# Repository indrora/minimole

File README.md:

# miniMOLE: the miniature Modular Output for Legacy Electronics.

the MiniMOLE is a tiny power supply for powering hard drives, floppy drives, etc. on the go. 

The power supplies that a lot of powerable HDD docks come with are just not good enough to handle some drives. Other times, you need something that doesn't fit in one of those docks. 

The miniMOLE is here for that: Either use a cablemod RT/Seasonic style modular peripheral cable or the included push-fit connectors for custom stuff. 

## fab notes:

* 2oz copper
* OSP or ENIG finish
* Everything has a JLCPCB part number.

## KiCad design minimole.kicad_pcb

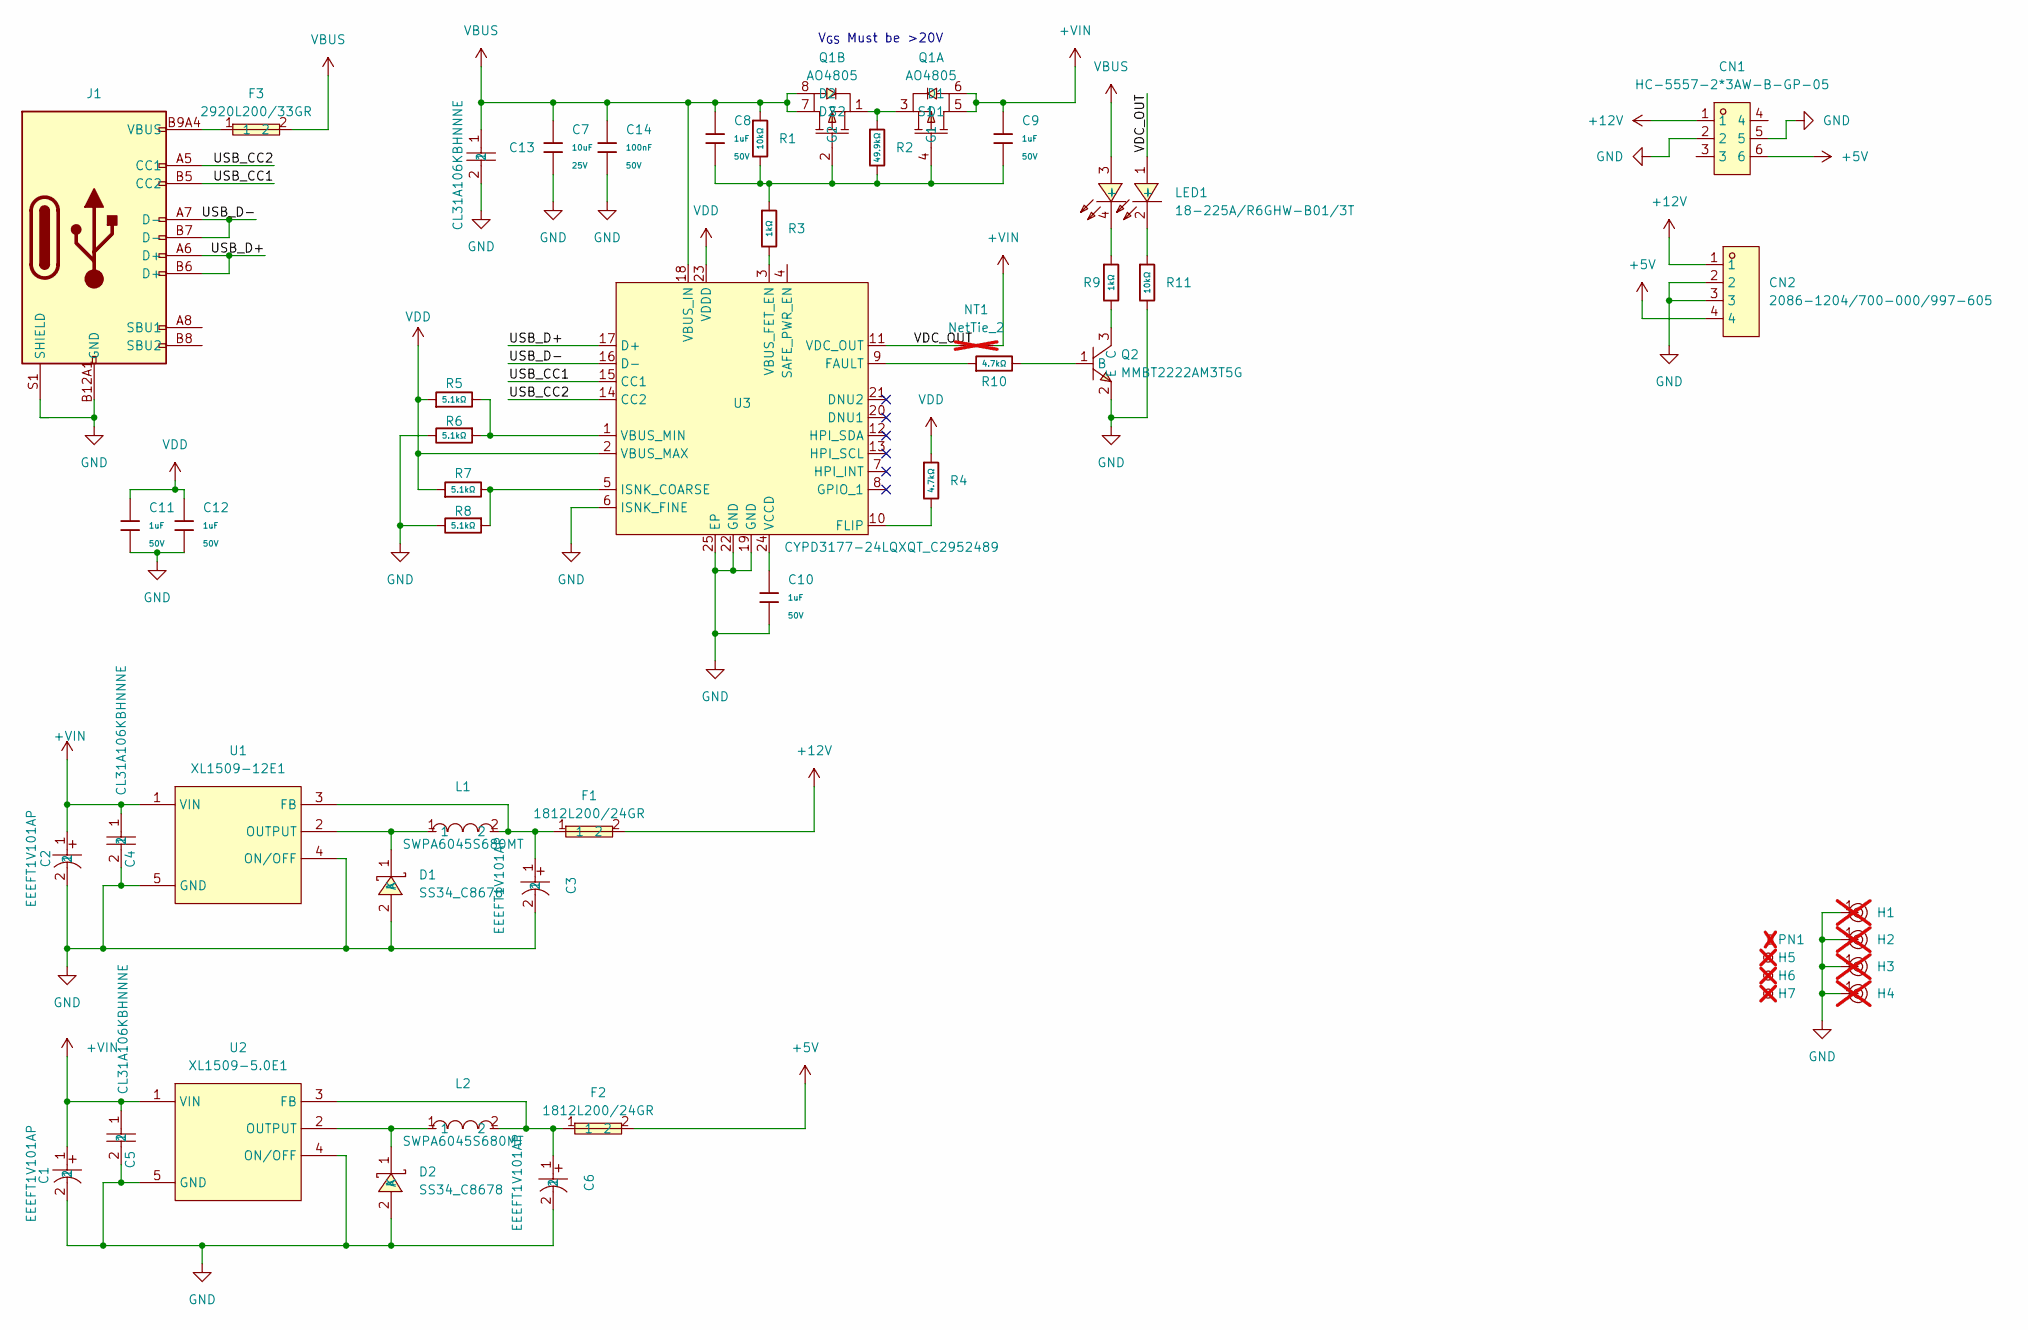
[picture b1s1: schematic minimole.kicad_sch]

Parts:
C1, C2, C3, C6: EEEFT1V101AP; CAP-SMD_BD6.3-L6.6-W6.6-FD; MPN EEEFT1V101AP; LCSC Part C128464
C4, C5, C13: CL31A106KBHNNNE; C1206; MPN CL31A106KBHNNNE; LCSC Part C13585
C7: 10uF; C_0603; Voltage Rated 25V; Tolerance ±20%; Part CL10A106MA8NRNC; LCSC C96446
C8, C9, C10, C11, C12: 1uF; C_0603; Voltage Rated 50V; Tolerance ±10%; Part CL10A105KB8NNNC; LCSC C15849
C14: 100nF; C_0603; Voltage Rated 50V; Tolerance ±10%; Part CC0603KRX7R9BB104; LCSC C14663
CN1: HC-5557-2*3AW-B-GP-05; CONN-TH_6P-P4.20_HCTL_HC-5557-2X3AW-B-GP-05; MPN HC-5557-2*3AW-B-GP-05; LCSC Part C22398227
CN2: 2086-1204/700-000/997-605; CONN-SMD_4P-P3.50_2086-1204; MPN 2086-1204/700-000/997-605; LCSC Part C3309718
D1, D2: SS34_C8678; SMA_L4.3-W2.6-LS5.2-RD; MPN SS34; LCSC Part C8678
F1, F2: 1812L200/24GR; F1812; MPN 1812L200/24GR; LCSC Part C18198341
F3: 2920L200/33GR; F2920; MPN 2920L200/33GR; LCSC Part C19078743
H1, H2, H3, H4: Hole, 3mm; not fitted
H5, H6, H7: Hole_Tooling_JLCPCB; not fitted
J1: Connector, USB-TYPE-C-16P; TYPE-C-SMD_HX-TYPE-C-16PIN; LCSC C2927039
L1, L2: SWPA6045S680MT; IND-SMD_L6.0-W6.0_SWPA6045S; MPN SWPA6045S680MT; LCSC Part C53663
LED1: 18-225A/R6GHW-B01/3T; LED-ARRAY-SMD_4P-L1.6-W0.8-BR-RD-2; MPN 18-225A/R6GHW-B01/3T; LCSC Part C648675
NT1: NetTie_2; NetTie-2_SMD_Pad0.5mm; not fitted
PN1: Part_Num_JLCPCB; not fitted
Q1: AO4805; SOIC-8_L4.9-W3.9-P1.27-LS6.0-BL; MPN AO4805; LCSC Part C38943
Q2: MMBT2222AM3T5G; SOT-723-3_L1.2-W0.8-P0.80-LS1.2-BR; MPN MMBT2222AM3T5G; LCSC Part C896289
R1, R11: 10kΩ; R_0402; Overload Voltage (Max) 50V; Tolerance ±1%; Part 0402WGF1002TCE; LCSC C25744
R2: 49.9kΩ; R_0402; Overload Voltage (Max) 50V; Tolerance ±1%; Part 0402WGF4992TCE; LCSC C25897
R3, R9: 1kΩ; R_0402; Overload Voltage (Max) 50V; Tolerance ±1%; Part 0402WGF1001TCE; LCSC C11702
R4, R10: 4.7kΩ; R_0402; Overload Voltage (Max) 50V; Tolerance ±1%; Part 0402WGF4701TCE; LCSC C25900
R5, R6, R7, R8: 5.1kΩ; R_0402; Overload Voltage (Max) 50V; Tolerance ±1%; Part 0402WGF5101TCE; LCSC C25905
U1: XL1509-12E1; SOIC-8_L5.0-W4.0-P1.27-LS6.0-BL; MPN XL1509-12E1; LCSC Part C62594
U2: XL1509-5.0E1; SOIC-8_L5.0-W4.0-P1.27-LS6.0-BL; MPN XL1509-5.0E1; LCSC Part C61063
U3: CYPD3177-24LQXQT_C2952489; TQFN-24_L4.0-W4.0-P0.50-TL-EP2.8; MPN CYPD3177-24LQXQT; LCSC Part C2952489

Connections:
+5V: CN1.6, CN2.4, F2.2
+12V: CN1.1, CN2.1, F1.2
+VIN: C1.1, C2.1, C4.1, C5.1, C9.1, NT1.2, Q1.5 (D1), Q1.6 (D1), U1.1 (VIN), U2.1 (VIN)
/USB_CC1: J1.B5 (CC2), U3.15 (CC1)
/USB_CC2: J1.A5 (CC1), U3.14 (CC2)
/USB_D+: J1.A6 (D+), J1.B6 (D+), U3.17 (D+)
/USB_D-: J1.A7 (D-), J1.B7 (D-), U3.16 (D-)
/VDC_OUT: LED1.1 (+), NT1.1, U3.11 (VDC_OUT)
GND: C1.2, C2.2, C3.2, C4.2, C5.2, C6.2, C7.2, C10.2, C11.2, C12.2, C13.2, C14.2, CN1.2, CN1.5, CN2.2, CN2.3, D1.2 (A), D2.2 (A), H1.1, H2.1, H3.1, H4.1, J1.A12B1 (GND), J1.B12A1 (GND), J1.S1 (SHIELD), Q2.2 (E), R6.2, R8.2, R11.2, U1.4 (ON/OFF), U1.5 (GND), U1.6 (GND), U1.7 (GND), U1.8 (GND), U2.4 (ON/OFF), U2.5 (GND), U2.6 (GND), U2.7 (GND), U2.8 (GND), U3.6 (ISNK_FINE), U3.19 (GND), U3.22 (GND), U3.25 (EP)
unnamed: D1.1 (K), L1.1, U1.2 (OUTPUT)
unnamed: D2.1 (K), L2.1, U2.2 (OUTPUT)
unnamed: F3.1, J1.A9B4 (VBUS), J1.B9A4 (VBUS)
unnamed: LED1.2 (-), R11.1
unnamed: LED1.4 (-), R9.1
unnamed: C8.2, C9.2, Q1.2 (G2), Q1.4 (G1), R1.2, R2.2, R3.1
unnamed: Q1.1 (S2), Q1.3 (S1), R2.1
unnamed: Q2.1 (B), R10.2
unnamed: Q2.3 (C), R9.2
unnamed: C3.1, F1.1, L1.2, U1.3 (FB)
unnamed: C6.1, F2.1, L2.2, U2.3 (FB)
unnamed: R10.1, U3.9 (FAULT)
unnamed: R4.2, U3.10 (FLIP)
unnamed: R7.2, R8.1, U3.5 (ISNK_COARSE)
unnamed: R3.2, U3.3 (VBUS_FET_EN)
unnamed: R5.2, R6.1, U3.1 (VBUS_MIN)
unnamed: C10.1, U3.24 (VCCD)
VBUS: C7.1, C8.1, C13.1, C14.1, F3.2, LED1.3 (+), Q1.7 (D2), Q1.8 (D2), R1.1, U3.18 (VBUS_IN)
VDD: C11.1, C12.1, R4.1, R5.1, R7.1, U3.2 (VBUS_MAX), U3.23 (VDDD)

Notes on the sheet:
V_{GS} Must be >20V

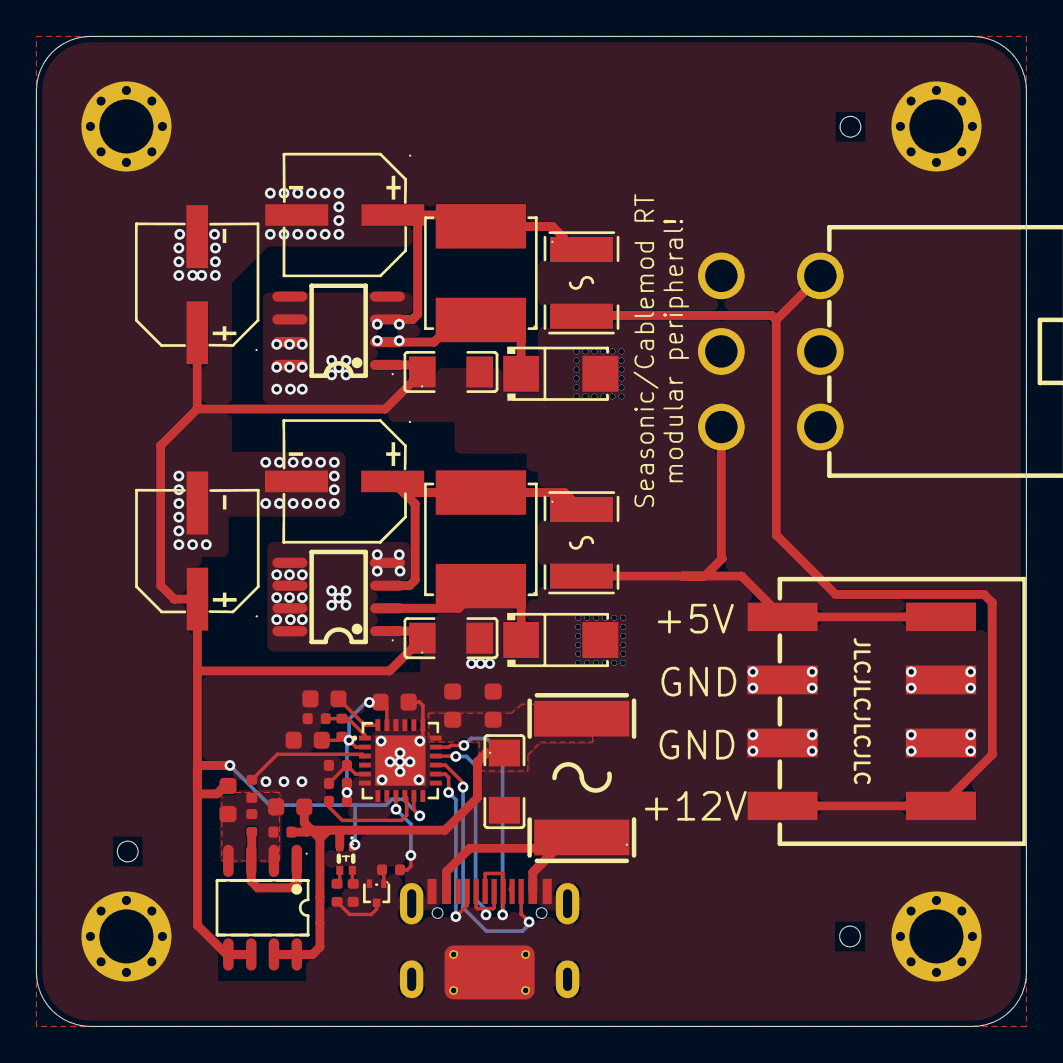
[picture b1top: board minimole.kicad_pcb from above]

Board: 2 copper layers, 55.0 x 55.0 mm, 50 parts (0 on the bottom side), 28 nets.

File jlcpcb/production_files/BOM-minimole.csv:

Comment,Designator,Footprint,LCSC,Quantity
100nF,C14,C_0603,C14663,1
10kΩ,"R1,R11",R_0402,C25744,2
10uF,C7,C_0603,C96446,1
18-225A/R6GHW-B01/3T,LED1,LED-ARRAY-SMD_4P-L1.6-W0.8-BR-RD-2,C648675,1
1812L200/24GR,"F1,F2",F1812,C18198341,2
1kΩ,"R3,R9",R_0402,C11702,2
1uF,"C10,C11,C12,C8,C9",C_0603,C15849,5
2086-1204/700-000/997-605,CN2,CONN-SMD_4P-P3.50_2086-1204,C3309718,1
2920L200/33GR,F3,F2920,C19078743,1
4.7kΩ,"R10,R4",R_0402,C25900,2
49.9kΩ,R2,R_0402,C25897,1
5.1kΩ,"R5,R6,R7,R8",R_0402,C25905,4
AO4805,Q1,SOIC-8_L4.9-W3.9-P1.27-LS6.0-BL,C38943,1
CL31A106KBHNNNE,"C13,C4,C5",C1206,C13585,3
CYPD3177-24LQXQT_C2952489,U3,TQFN-24_L4.0-W4.0-P0.50-TL-EP2.8,C2952489,1
"Connector, USB-TYPE-C-16P",J1,TYPE-C-SMD_HX-TYPE-C-16PIN,C2927039,1
EEEFT1V101AP,"C1,C2,C3,C6",CAP-SMD_BD6.3-L6.6-W6.6-FD,C128464,4
HC-5557-2*3AW-B-GP-05,CN1,CONN-TH_6P-P4.20_HCTL_HC-5557-2X3AW-B-GP-05,C22398227,1
MMBT2222AM3T5G,Q2,SOT-723-3_L1.2-W0.8-P0.80-LS1.2-BR,C896289,1
SS34_C8678,"D1,D2",SMA_L4.3-W2.6-LS5.2-RD,C8678,2
SWPA6045S680MT,"L1,L2",IND-SMD_L6.0-W6.0_SWPA6045S,C53663,2
XL1509-12E1,U1,SOIC-8_L5.0-W4.0-P1.27-LS6.0-BL,C62594,1
XL1509-5.0E1,U2,SOIC-8_L5.0-W4.0-P1.27-LS6.0-BL,C61063,1
